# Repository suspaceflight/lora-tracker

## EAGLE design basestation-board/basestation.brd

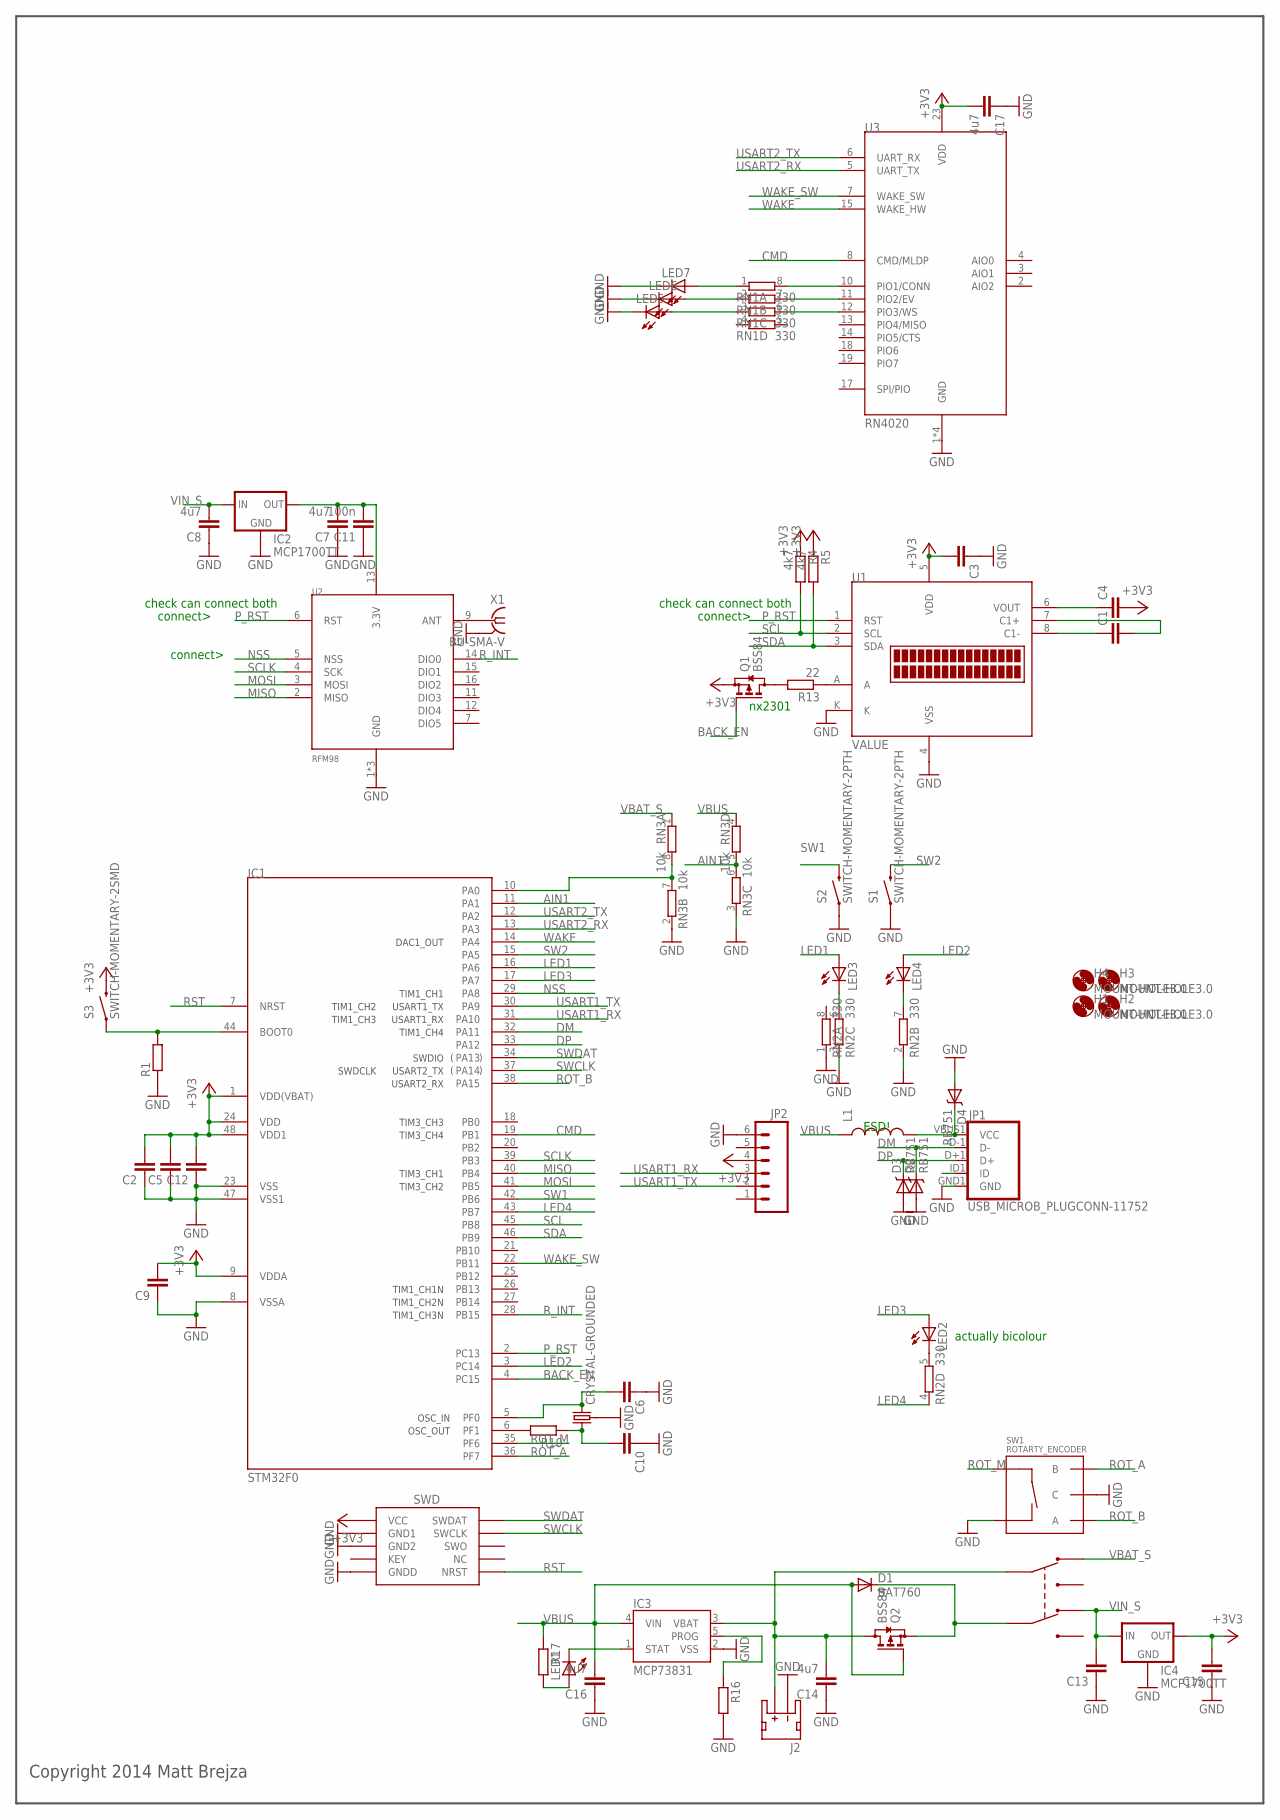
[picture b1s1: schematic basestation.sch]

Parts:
C1, C2, C3, C4, C5, C6, C9, C10, C12, C13, C15: C-EUC0603; C0603
C7, C8, C14, C16, C17: 4u7; C0603
C11: 100n; C0603
D1: BAT760; SOD323-R
D2, D3, D4: RB751; SOD-523
H1, H2, H3, H4: MOUNT-HOLE3.0; 3,0
IC1: STM32F0; TQFP48
IC2, IC4: MCP1700TT; SOT23
IC3: MCP73831; SOT23-5
J1: SWD_SHROUD_SMD; SWD_SMD_SHROUD
J2: JST_2MM_MALE; JST-2-SMD
JP1: USB_MICROB_PLUGCONN-11752; USB-B-MICRO-SMD_V03
JP2: M06SMD; 1X06-SMD
L1: INDUCTOR0603; 0603
LED1, LED5, LED6, LED7: LEDCHIP-LED0805; CHIP-LED0805
LED2: LED5MM
LED3, LED4: LED3MM
Q1, Q2: BSS84; SOT23
R1, R10, R16, R17: R-EU_R0603; R0603
R4, R5: 4k7; R0603
R13: 22; R0603
RN1, RN2: 330; EXB38V
RN3: 10k; EXB38V
S1, S2: SWITCH-MOMENTARY-2PTH; TACTILE-PTH
S3: SWITCH-MOMENTARY-2SMD; TACTILE_SWITCH_SMD
SW1: ROTARTY_ENCODER; ROTARY_ENC_PLAIN
U1: NHD-C0216CIZ-FSW
U2: RFM98; RFM97
U3: RN4020
U$1: DPDTSLIDE
X1: BU-SMA-V
X2: CRYSTAL-GROUNDED; CRYSTAL-SMD-5X3

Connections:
3.3V: C7.2, C11.2, IC2.2 (OUT), U2.13 (3.3V)
+3V3: C2.2, C3.2, C4.2, C5.2, C9.2, C12.2, C15.2, C17.2, IC1.1 (VDD(VBAT)), IC1.9 (VDDA), IC1.24 (VDD), IC1.48 (VDD1), IC4.2 (OUT), J1.1 (VCC), JP2.4, Q1.2 (S), R4.1, R5.1, S3.3 (2), U1.5 (VDD), U3.23 (VDD)
AIN1: IC1.11 (PA1), RN3.5 (2), RN3.6 (2)
BACK_EN: IC1.4 (PC15), Q1.1 (G)
CMD: IC1.19 (PB1), U3.8 (CMD/MLDP)
DM: D2.C, IC1.32 (PA11), JP1.D-1 (D-)
DP: D3.C, IC1.33 (PA12), JP1.D+1 (D+)
GND: C2.1, C3.1, C5.1, C6.1, C7.1, C8.1, C9.1, C10.1, C11.1, C12.1, C13.1, C14.1, C15.1, C16.1, C17.1, D2.A, D3.A, D4.A, IC1.8 (VSSA), IC1.23 (VSS), IC1.47 (VSS1), IC2.1 (GND), IC3.2 (VSS), IC4.1 (GND), J1.3 (GND1), J1.5 (GND2), J1.9 (GNDD), J2.1 (-), JP1.GND1 (GND), JP2.6, LED5.C, LED6.C, LED7.C, R1.1, R16.2, RN2.1, RN2.2 (1), RN2.3 (1), RN3.2 (1), RN3.3 (1), S1.1, S2.1, SW1.C, SW1.SW-, U1.4 (VSS), U1.K, U2.1 (GND), U2.8 (GND), U2.10 (GND), U3.1 (GND), U3.9 (GND), U3.16 (GND), U3.24 (GND), X1.2, X1.3 (2), X1.4 (2), X1.5 (2), X2.2 (3), X2.4 (3)
LED1: IC1.16 (PA6), LED3.A
LED2: IC1.3 (PC14), LED4.A
LED3: IC1.17 (PA7), LED2.A
LED4: IC1.43 (PB7), RN2.4 (1)
MISO: IC1.40 (PB4), U2.2 (MISO)
MOSI: IC1.41 (PB5), U2.3 (MOSI)
unnamed: U2.9 (ANT), X1.1
unnamed: D1.C, Q2.2 (S), U$1.2X (COM1)
unnamed: Q1.3 (D), R13.2
unnamed: IC1.44 (BOOT0), R1.2, S3.1
unnamed: RN1.8 (2), U3.10 (PIO1/CONN)
unnamed: LED3.K (C), RN2.6 (2)
unnamed: IC3.5 (PROG), R16.1
unnamed: C1.1, U1.8 (C1-)
unnamed: C1.2, U1.7 (C1+)
unnamed: LED4.K (C), RN2.7 (2)
unnamed: LED2.K (C), RN2.5 (2)
unnamed: C4.1, U1.6 (VOUT)
unnamed: RN1.7 (2), U3.11 (PIO2/EV)
unnamed: RN1.6 (2), U3.12 (PIO3/WS)
unnamed: LED7.A, RN1.1
unnamed: LED6.A, RN1.2 (1)
unnamed: LED5.A, RN1.3 (1)
unnamed: R13.1, U1.A
unnamed: IC1.10 (PA0), RN3.7 (2), RN3.8 (2)
unnamed: IC3.1 (STAT), LED1.C
unnamed: IC1.6 (PF1), R10.2
unnamed: C6.2, IC1.5 (PF0), X2.1 (2)
unnamed: C10.2, R10.1, X2.3 (1)
unnamed: C14.2, IC3.3 (VBAT), J2.2 (+), Q2.3 (D), U$1.1X (COM0)
unnamed: LED1.A, R17.2
unnamed: D4.C, JP1.VBUS1 (VCC), L1.2
NSS: IC1.29 (PA8), U2.5 (NSS)
P_RST: IC1.2 (PC13), U1.1 (RST), U2.6 (RST)
ROT_A: IC1.36 (PF7), SW1.B
ROT_B: IC1.38 (PA15), SW1.A
ROT_M: IC1.35 (PF6), SW1.SW+
RST: IC1.7 (NRST), J1.10 (NRST)
R_INT: IC1.28 (PB15), U2.14 (DIO0)
SCL: IC1.45 (PB8), R4.2, U1.2 (SCL)
SCLK: IC1.39 (PB3), U2.4 (SCK)
SDA: IC1.46 (PB9), R5.2, U1.3 (SDA)
SW1: IC1.42 (PB6), S2.3 (2)
SW2: IC1.15 (PA5), S1.3 (2)
SWCLK: IC1.37 (PA14), J1.4 (SWCLK)
SWDAT: IC1.34 (PA13), J1.2 (SWDAT)
USART1_RX: IC1.31 (PA10), JP2.3
USART1_TX: IC1.30 (PA9), JP2.2
USART2_RX: IC1.13 (PA3), U3.5 (UART_TX)
USART2_TX: IC1.12 (PA2), U3.6 (UART_RX)
VBAT_S: RN3.1, U$1.1A (NC0)
VBUS: C16.2, D1.A, IC3.4 (VIN), L1.1, Q2.1 (G), R17.1, RN3.4 (1)
VIN_S: C8.2, C13.2, IC2.3 (IN), IC4.3 (IN), U$1.2A (NC1)
WAKE: IC1.14 (PA4), U3.15 (WAKE_HW)
WAKE_SW: IC1.22 (PB11), U3.7 (WAKE_SW)

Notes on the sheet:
actually bicolour
connect>
nx2301
ESD!
check can connect both
Copyright 2014 Matt Brejza

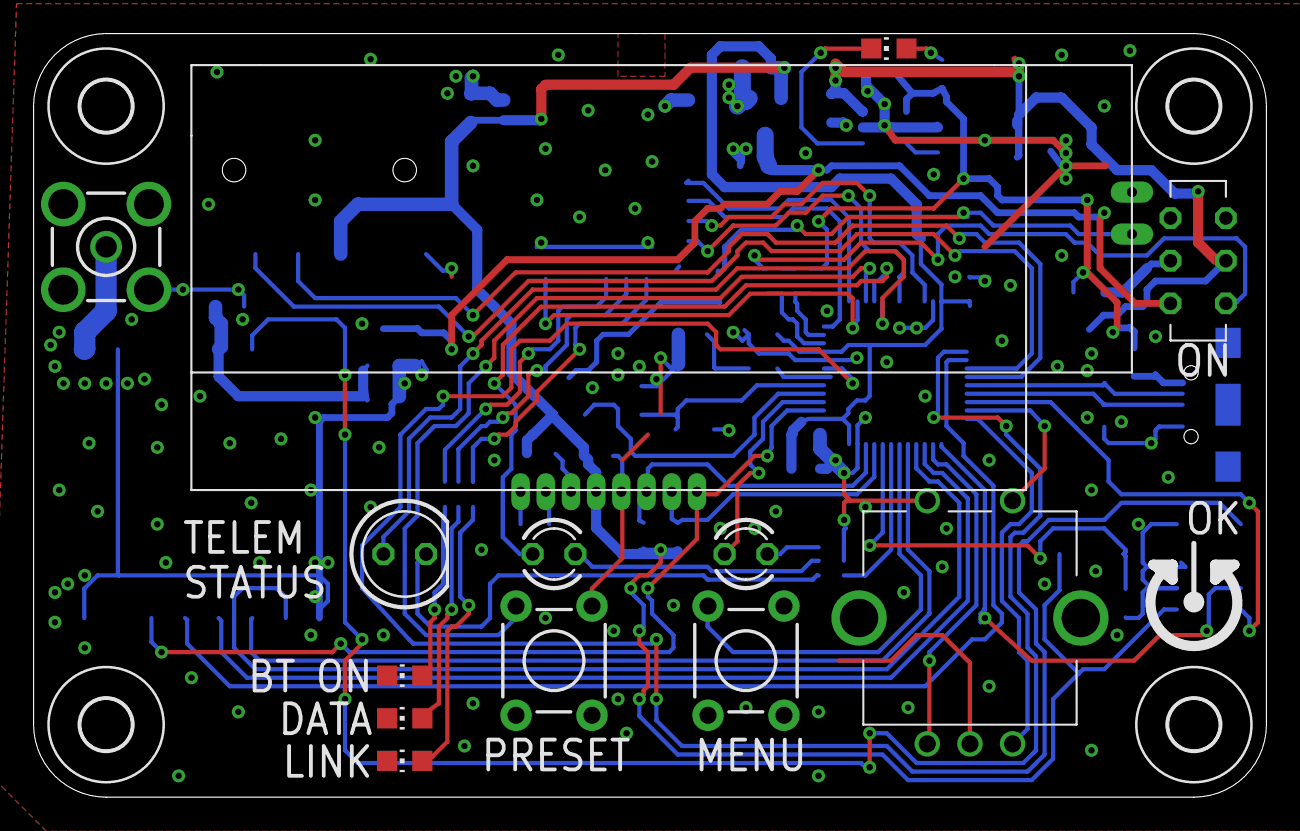
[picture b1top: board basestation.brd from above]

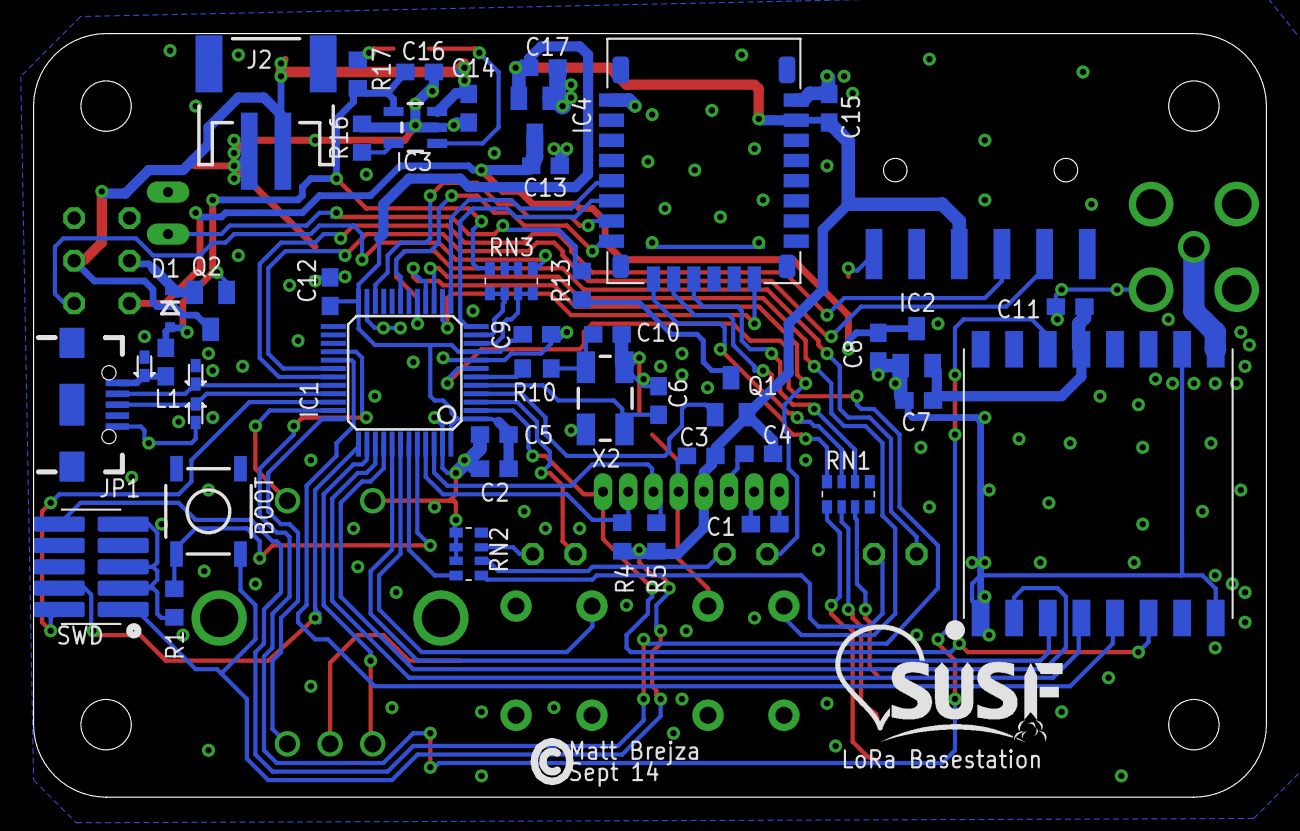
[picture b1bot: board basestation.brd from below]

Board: 2 copper layers, 73.4 x 45.5 mm, 64 parts (47 on the bottom side), 63 nets.

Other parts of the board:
U$2: SUSF-XSM

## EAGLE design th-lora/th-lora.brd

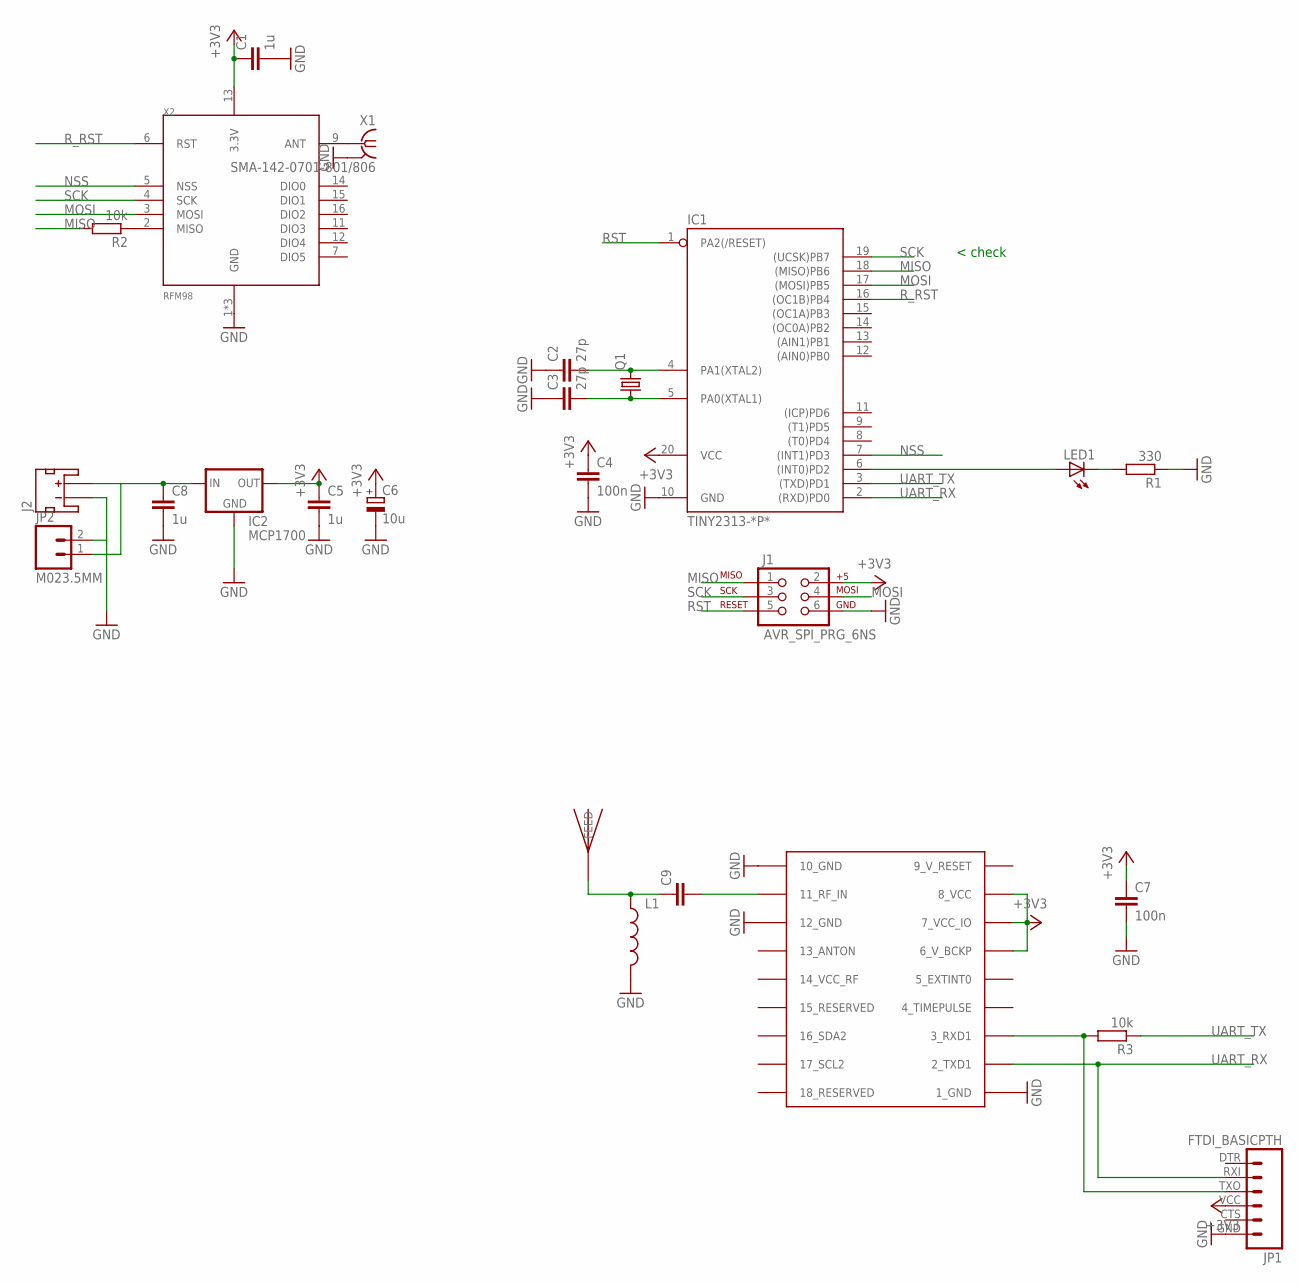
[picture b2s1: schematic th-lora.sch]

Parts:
C1, C5, C8: 1u; C050-025X075
C2, C3: 27p; C050-025X075
C4, C7: 100n; C050-025X075
C6: 10u; E2,5-5
C9: C-EUC0603; C0603
IC1: TINY2313-*P*; DIL20
IC2: MCP1700; TO92-INLINE
J1: AVR_SPI_PRG_6NS; 2X3-NS
J2: JST_2MM_MALE; JST-2-SMD
JP1: FTDI_BASICPTH; FTDI_BASIC
JP2: M023.5MM; SCREWTERMINAL-3.5MM-2
L1: INDUCTOR0603; 0603
LED1: LED3MM
Q1: CRYSTALHC49S; HC49/S
R1: 330; 0204/7
R2, R3: 10k; 0204/7
U$3: JTI_ANTENNA-1575AT43A40
X1: SMA-142-0701-801/806; J502-ND-142-0701-801/806
X2: RFM98; RFM97
X3: UBLOX_MAX

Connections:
9_V_RESET: X3.9_V_RESET
+3V3: C1.1, C4.1, C5.1, C6.+, C7.1, IC1.20 (VCC), IC2.VOUT (OUT), J1.2, JP1.VCC (4), X2.13 (3.3V), X3.6_V_BCKP, X3.7_VCC_IO, X3.8_VCC
GND: C1.2, C2.1, C3.1, C4.2, C5.2, C6.-, C7.2, C8.2, IC1.10 (GND), IC2.GND, J1.6, J2.1 (-), JP1.GND (6), JP2.2, L1.2, R1.1, X1.G@1 (2), X1.G@2 (2), X1.G@3 (2), X1.G@4 (2), X2.1 (GND), X2.8 (GND), X2.10 (GND), X3.1_GND, X3.10_GND, X3.12_GND
MISO: IC1.18 ((MISO)PB6), J1.1, R2.2
MOSI: IC1.17 ((MOSI)PB5), J1.4, X2.3 (MOSI)
unnamed: C9.2, X3.11_RF_IN
unnamed: X1.1, X2.9 (ANT)
unnamed: LED1.K (C), R1.2
unnamed: C9.1, L1.1, U$3.FEED
unnamed: C2.2, IC1.4 (PA1(XTAL2)), Q1.2
unnamed: C3.2, IC1.5 (PA0(XTAL1)), Q1.1
unnamed: C8.1, IC2.VIN (IN), J2.2 (+), JP2.1
unnamed: IC1.6 ((INT0)PD2), LED1.A
unnamed: JP1.TXO (3), R3.2, X3.3_RXD1
unnamed: R2.1, X2.2 (MISO)
NSS: IC1.7 ((INT1)PD3), X2.5 (NSS)
RST: IC1.1 (PA2(/RESET)), J1.5
R_RST: IC1.16 ((OC1B)PB4), X2.6 (RST)
SCK: IC1.19 ((UCSK)PB7), J1.3, X2.4 (SCK)
UART_RX: IC1.2 ((RXD)PD0), JP1.RXI (2), X3.2_TXD1
UART_TX: IC1.3 ((TXD)PD1), R3.1

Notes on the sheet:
< check

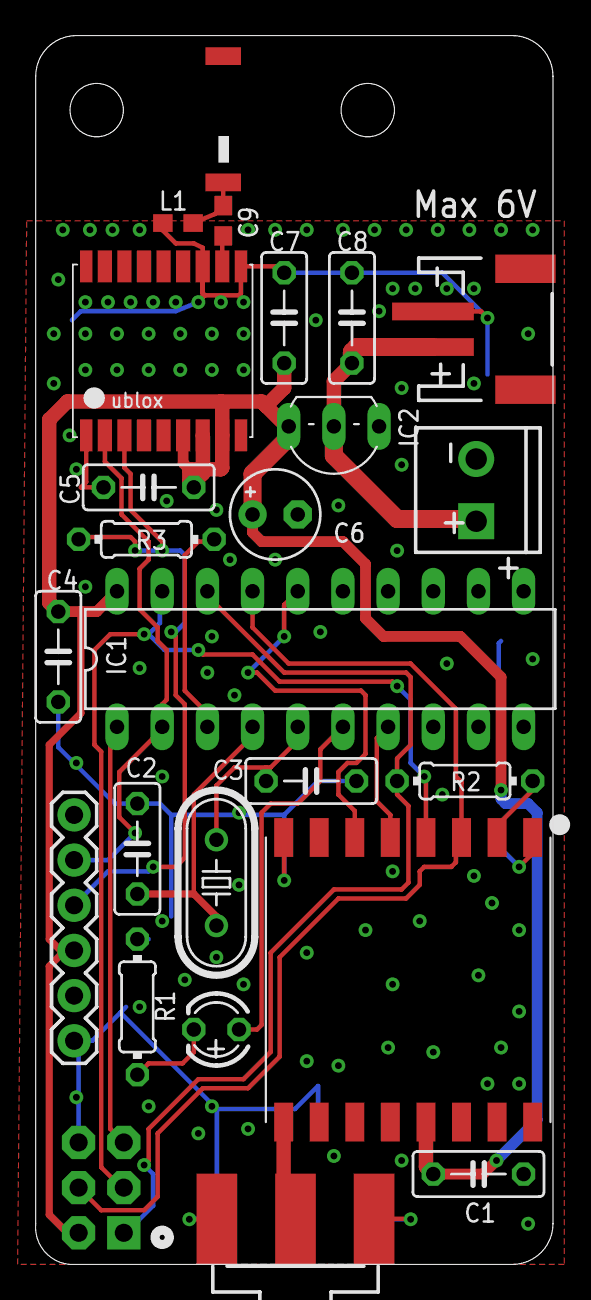
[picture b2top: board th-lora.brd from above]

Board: 2 copper layers, 29.1 x 69.1 mm, 26 parts (1 on the bottom side), 20 nets.

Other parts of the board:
U$4: SUSF-XSM

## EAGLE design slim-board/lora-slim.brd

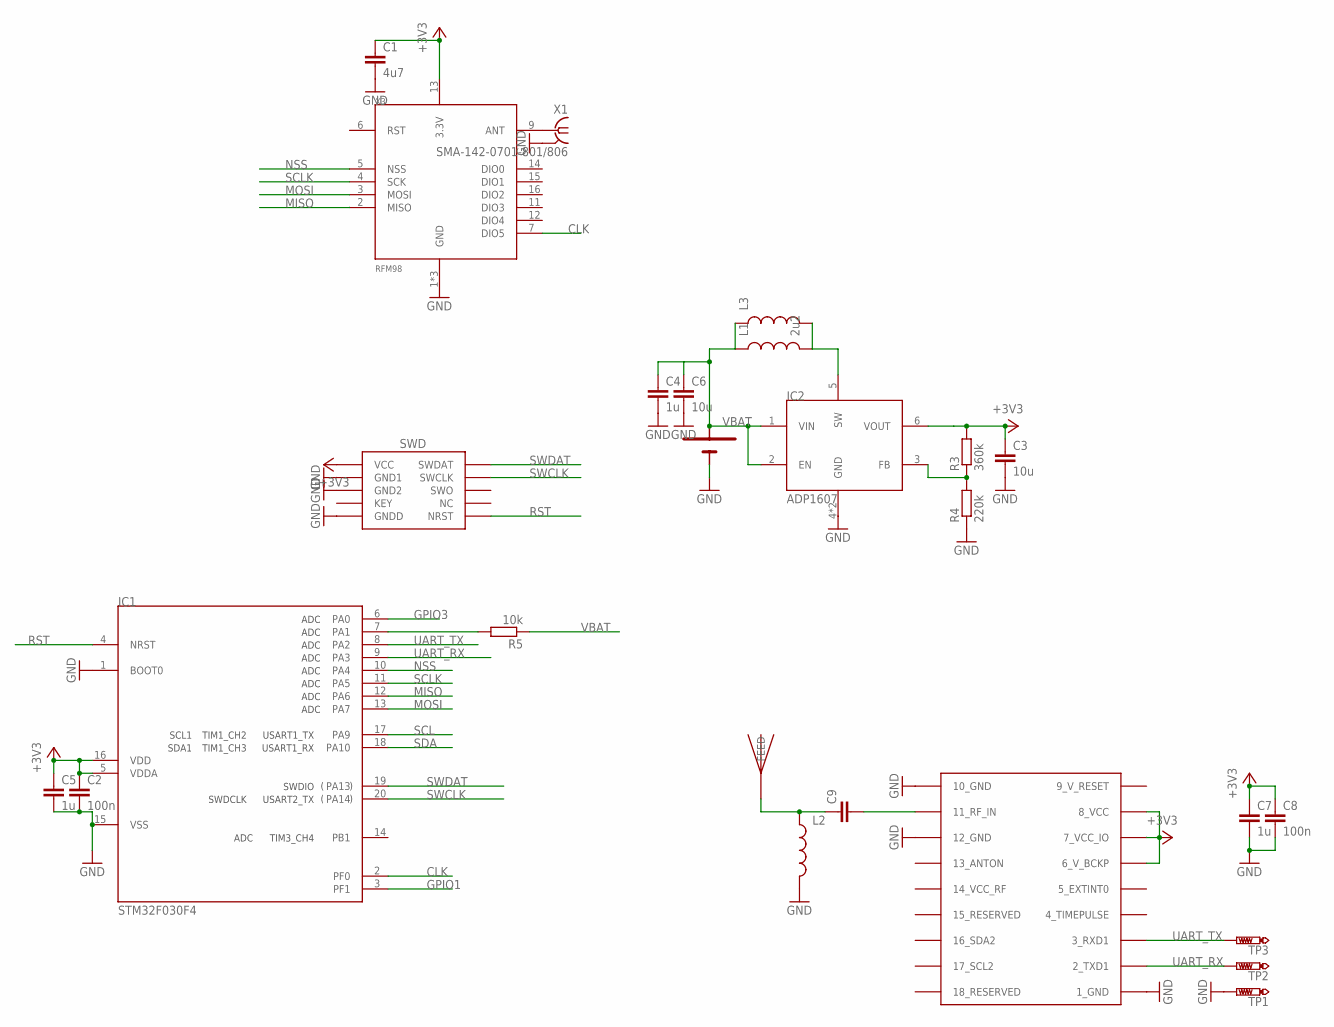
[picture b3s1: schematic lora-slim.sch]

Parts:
C1: 4u7; C0603
C2, C8: 100n; C0603
C3, C6: 10u; C0805
C4, C5, C7: 1u; C0603
C9: C-EUC0603; C0603
IC1: STM32F030F4; TSSOP20
IC2: ADP1607; LFCSP6
J1: SWD_PTH_SHROUD
L1: 2u2; 0805
L2: INDUCTOR0603; 0603
L3: INDUCTOR1210; 1210
R3: 360k; R0603
R4: 220k; R0603
R5: 10k; R0603
TP1, TP2, TP3: PTR1B1,27; B1,27
U$5: JTI_ANTENNA-1575AT43A40
U$6: KEYSTONE-53; KEYSTONE53
X1: SMA-142-0701-801/806; J502-ND-142-0701-801/806
X2: UBLOX_MAX
X3: RFM98; RFM97

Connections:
9_V_RESET: X2.9_V_RESET
+3V3: C1.1, C2.1, C3.1, C5.1, C7.1, C8.1, IC1.5 (VDDA), IC1.16 (VDD), IC2.6 (VOUT), J1.1 (VCC), R3.2, X2.6_V_BCKP, X2.7_VCC_IO, X2.8_VCC, X3.13 (3.3V)
CLK: IC1.2 (PF0), X3.7 (DIO5)
GND: C1.2, C2.2, C3.2, C4.2, C5.2, C6.2, C7.2, C8.2, IC1.1 (BOOT0), IC1.15 (VSS), IC2.4 (GND), IC2.EP (GND), J1.3 (GND1), J1.5 (GND2), J1.9 (GNDD), L2.2, R4.1, TP1.TP, U$6.N1 (-), U$6.N2 (-), X1.G@1 (2), X1.G@2 (2), X1.G@3 (2), X1.G@4 (2), X2.1_GND, X2.10_GND, X2.12_GND, X3.1 (GND), X3.8 (GND), X3.10 (GND)
GPIO1: IC1.3 (PF1)
GPIO3: IC1.6 (PA0)
MISO: IC1.12 (PA6), X3.2 (MISO)
MOSI: IC1.13 (PA7), X3.3 (MOSI)
unnamed: C9.2, X2.11_RF_IN
unnamed: X1.1, X3.9 (ANT)
unnamed: IC2.5 (SW), L1.2, L3.2
unnamed: C9.1, L2.1, U$5.FEED
unnamed: IC2.3 (FB), R3.1, R4.2
unnamed: IC1.7 (PA1), R5.2
NSS: IC1.10 (PA4), X3.5 (NSS)
RST: IC1.4 (NRST), J1.10 (NRST)
SCL: IC1.17 (PA9)
SCLK: IC1.11 (PA5), X3.4 (SCK)
SDA: IC1.18 (PA10)
SWCLK: IC1.20 (PA14), J1.4 (SWCLK)
SWDAT: IC1.19 (PA13), J1.2 (SWDAT)
UART_RX: IC1.9 (PA3), TP2.TP, X2.2_TXD1
UART_TX: IC1.8 (PA2), TP3.TP, X2.3_RXD1
VBAT: C4.1, C6.1, IC2.1 (VIN), IC2.2 (EN), L1.1, L3.1, R5.1, U$6.P1 (+), U$6.P2 (+)

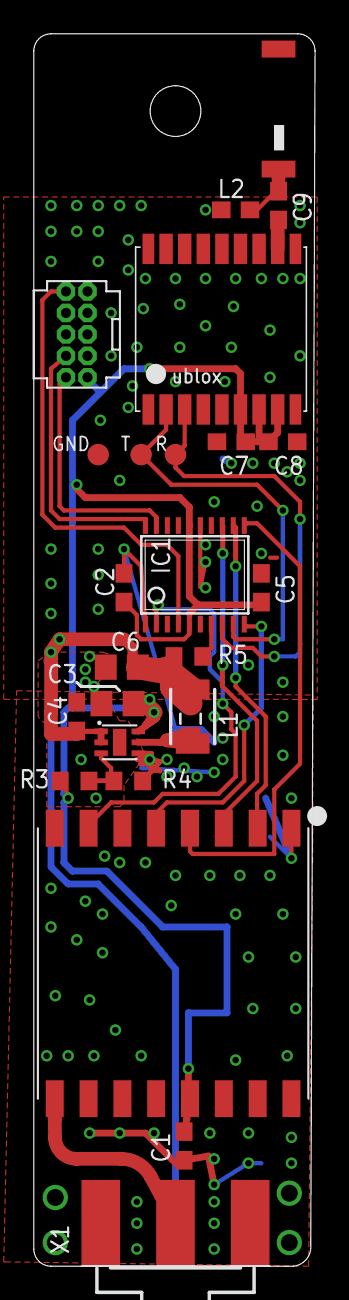
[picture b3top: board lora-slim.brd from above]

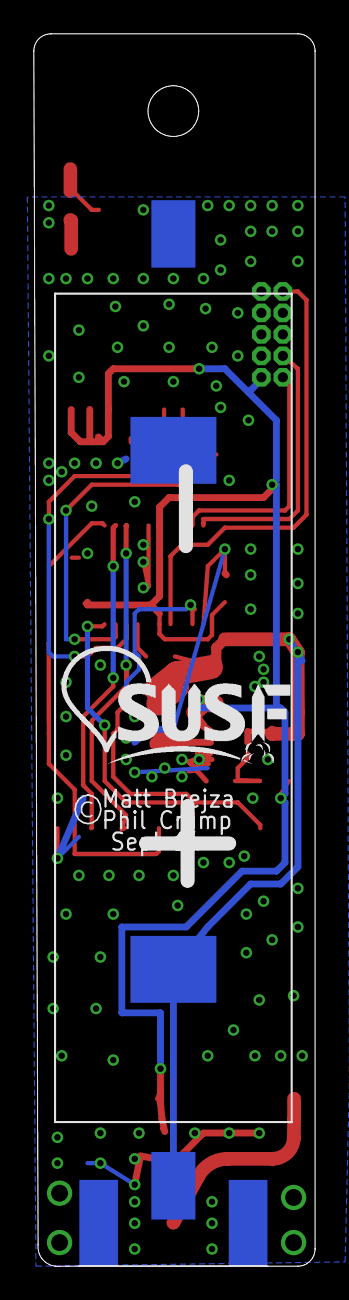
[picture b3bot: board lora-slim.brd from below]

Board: 2 copper layers, 16.6 x 72.9 mm, 27 parts (2 on the bottom side), 19 nets.

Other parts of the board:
U$1: SUSF-XSM

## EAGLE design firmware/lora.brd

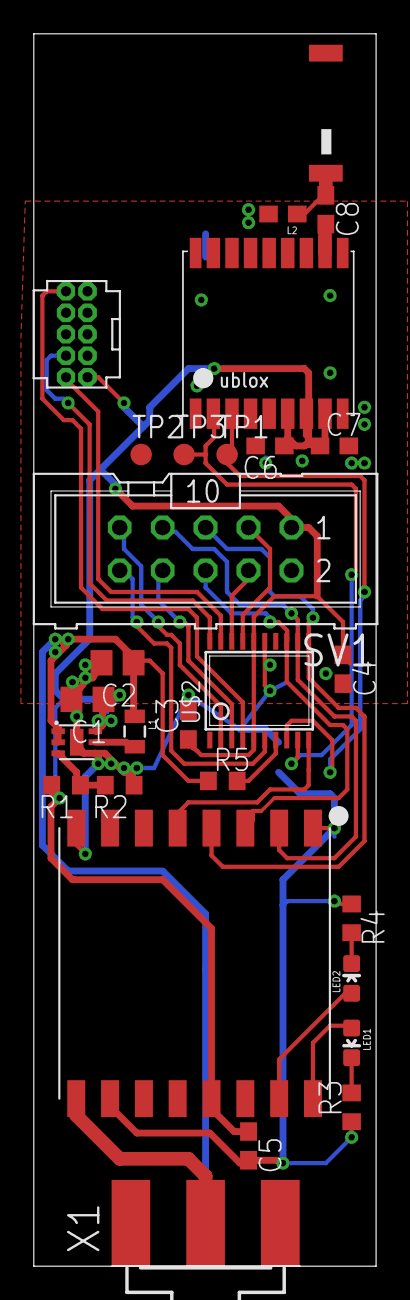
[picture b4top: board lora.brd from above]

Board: 2 copper layers, 20.2 x 72.9 mm, 29 parts (1 on the bottom side), 27 nets.

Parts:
C1, C2: C0805
C3, C4, C5, C6, C7, C8: C0603
J1: SWD_PTH_SHROUD
L1: 0805
L2: 0603
LED1, LED2: LED-0603
R1, R2, R3, R4, R5: R0603
SV1: ML10
TP1, TP2, TP3: PTR1B1,27; B1,27
U$1: KEYSTONE-53; KEYSTONE53
U$2: STM32F030F4; TSSOP20
U$3: UBLOX_MAX
U$4: JTI_ANTENNA-1575AT43A40
U$6: RFM98; RFM97
U$7: ADP1607; LFCSP6
X1: SMA-142-0701-801/806; J502-ND-142-0701-801/806

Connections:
+3V3: C1.1, C3.1, C4.1, C5.1, C6.1, C7.1, J1.1, R1.2, SV1.1, U$2.5, U$2.16, U$3.6_V_BCKP, U$3.7_VCC_IO, U$3.8_VCC, U$6.13, U$7.6
GND: C1.2, C2.2, C3.2, C4.2, C5.2, C6.2, C7.2, J1.3, J1.5, J1.9, L2.2, R2.1, R3.1, R4.1, SV1.2, TP2.TP, U$1.N1, U$1.N2, U$2.15, U$3.1_GND, U$3.10_GND, U$3.12_GND, U$6.1, U$6.8, U$6.10, U$7.4, U$7.EP
GPIO1: SV1.8, U$2.3
GPIO2: SV1.9, U$2.2
GPIO3: SV1.10, U$2.6
MISO: SV1.7, U$2.12, U$6.2
MOSI: SV1.6, U$2.13, U$6.3
unnamed: C8.2, U$3.11_RF_IN
unnamed: U$6.9, X1.1
unnamed: L1.2, U$7.5
unnamed: C8.1, L2.1, U$4.FEED
unnamed: LED1.C, R3.2
unnamed: R1.1, R2.2, U$7.3
unnamed: LED2.C, R4.2
unnamed: LED2.A, U$6.15
unnamed: R5.2, U$2.7
unnamed: LED1.A, U$6.16
NSS: U$2.10, U$6.5
RST: J1.10, U$2.4
SCL: SV1.3, U$2.17
SCLK: SV1.5, U$2.11, U$6.4
SDA: SV1.4, U$2.18
SWCLK: J1.4, U$2.20
SWDAT: J1.2, U$2.19
UART_RX: TP3.TP, U$2.9, U$3.2_TXD1
UART_TX: TP1.TP, U$2.8, U$3.3_RXD1
VBAT: C2.1, L1.1, R5.1, U$1.P1, U$1.P2, U$7.1, U$7.2

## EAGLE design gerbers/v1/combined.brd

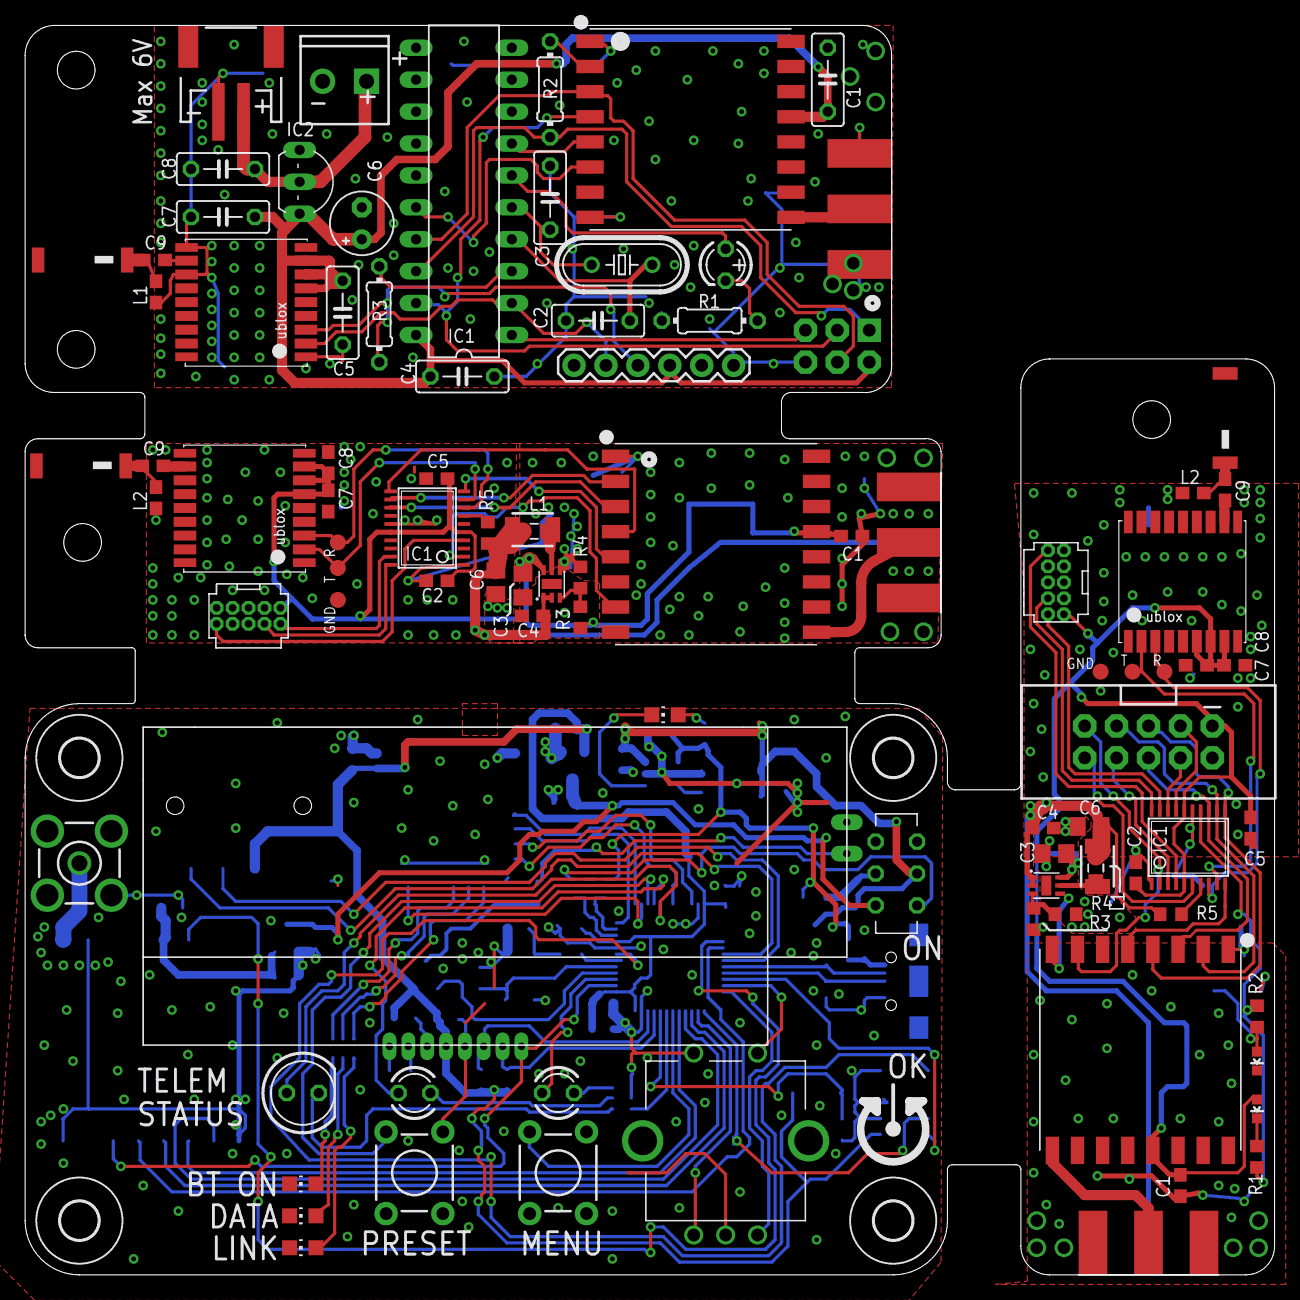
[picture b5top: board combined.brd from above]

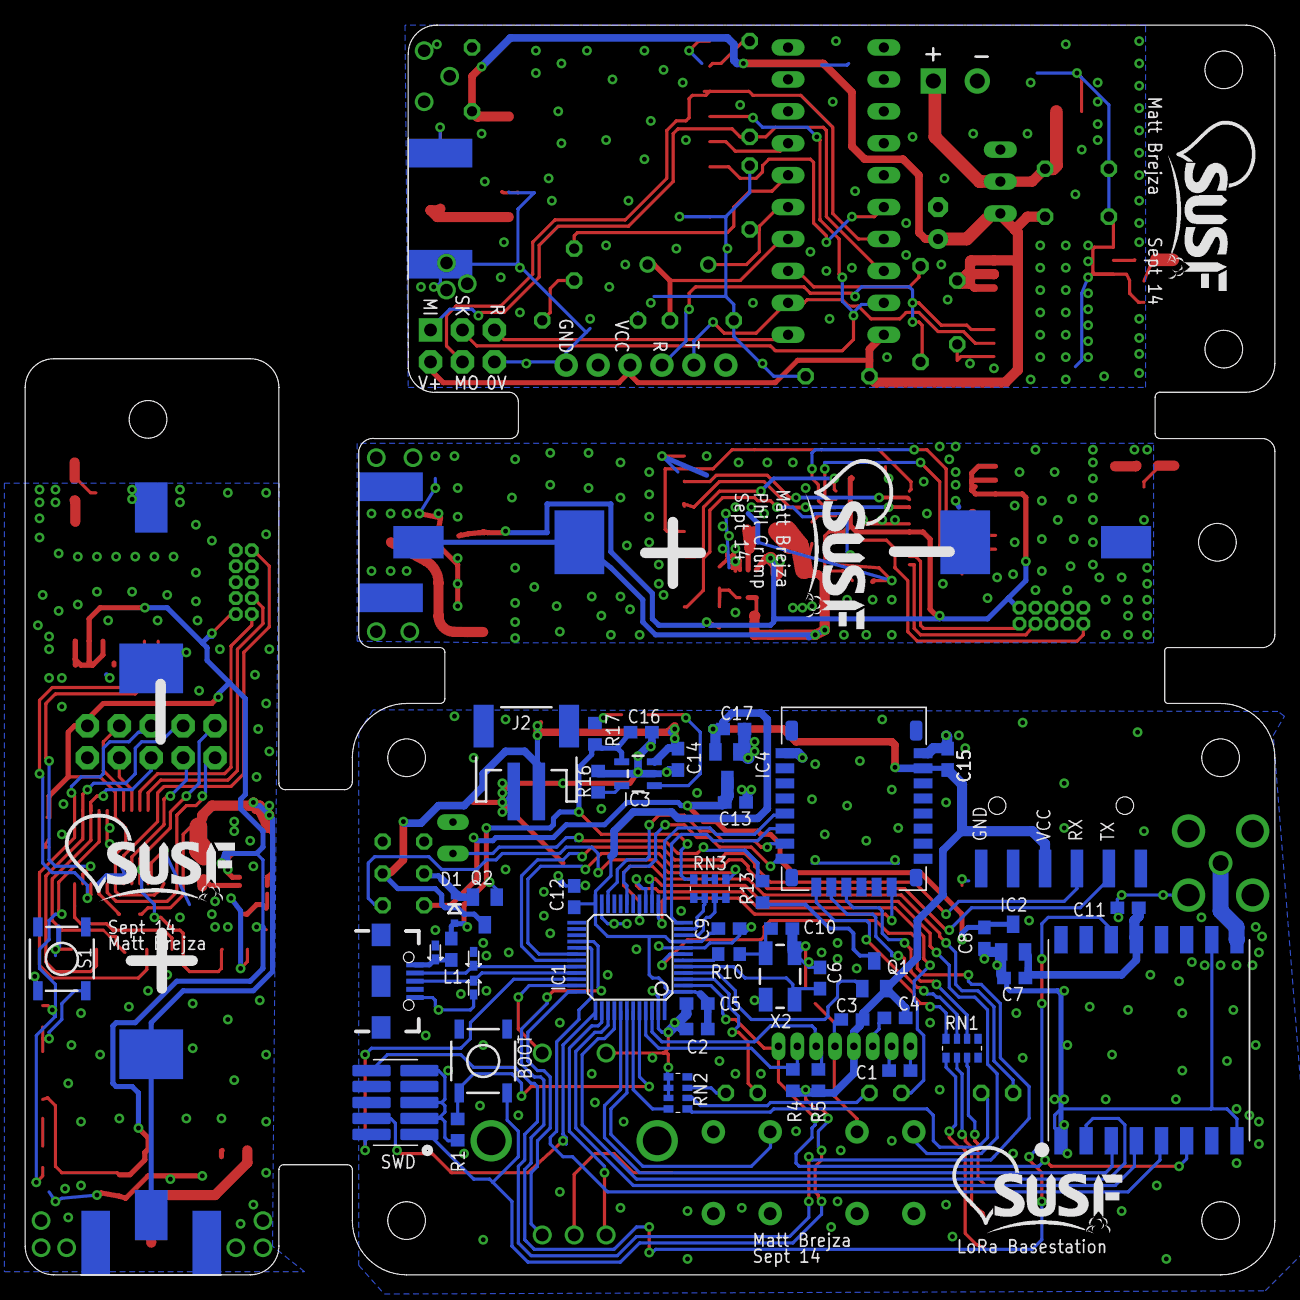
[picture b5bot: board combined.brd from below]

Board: 2 copper layers, 99.4 x 99.4 mm, 150 parts (53 on the bottom side), 127 nets.

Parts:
C1, C2, C3, C4, C5, C6, C9, C10, C12, C13, C15, C25, C34, C36: C0603
C7, C8, C14, C16, C17, C22, C31: 4u7; C0603
C11, C20, C24, C29, C33: 100n; C0603
C18, C19, C27, C28: 10u; C0805
C21, C23, C26, C30, C32, C35: 1u; C0603
C37, C42: 100n; C050-025X075
C38, C39, C43: 1u; C050-025X075
C40, C41: 27p; C050-025X075
C44: 10u; E2,5-5
D1: BAT760; SOD323-R
D2, D3, D4: RB751; SOD-523
H1, H2, H3, H4: MOUNT-HOLE3.0; 3,0
IC1: STM32F0; TQFP48
IC2, IC4: MCP1700TT; SOT23
IC3: MCP73831; SOT23-5
IC5, IC7: STM32F030F4; TSSOP20
IC6, IC8: ADP1607; LFCSP6
IC9: TINY2313-*P*; DIL20
IC10: MCP1700; TO92-INLINE
J1: SWD_SHROUD_SMD; SWD_SMD_SHROUD
J2, J6: JST-2-SMD
J3, J4: SWD_PTH_SHROUD
J5: AVR_SPI_PRG_6NS; 2X3-NS
JP1: USB_MICROB_PLUGCONN-11752; USB-B-MICRO-SMD_V03
JP2: 1X06-SMD
JP3: M05X2SHD; 2X5-SHROUDED
JP4: M023.5MM; SCREWTERMINAL-3.5MM-2
JP5: FTDI_BASICPTH; FTDI_BASIC
L1, L3, L6, L8: 0603
L2, L5: 2u2; 0805
L4, L7: 1210
LED1, LED5, LED6, LED7: CHIP-LED0805
LED2: LED5MM
LED3, LED4, LED10: LED3MM
LED8, LED9: LED-0603
Q1, Q2: BSS84; SOT23
Q3: HC49/S
R1, R10, R16, R17: R0603
R2, R11: 220k; R0603
R3, R9: 360k; R0603
R4, R5: 4k7; R0603
R6, R7: 330; R0603
R8, R12: 10k; R0603
R13: 22; R0603
R14: 330; 0204/7
R15, R18: 10k; 0204/7
RN1, RN2: 330; EXB38V
RN3: 10k; EXB38V
S1, S2: SWITCH-MOMENTARY-2PTH; TACTILE-PTH
S3, S4: SWITCH-MOMENTARY-2SMD; TACTILE_SWITCH_SMD
SW1: ROTARTY_ENCODER; ROTARY_ENC_PLAIN
TP1, TP2, TP3, TP4, TP5, TP6: PTR1B1,27; B1,27
U1: NHD-C0216CIZ-FSW
U2: RFM98; RFM97
U3: RN4020
U$1: DPDTSLIDE
U$2, U$3, U$8, U$10: SUSF-XSM
U$4, U$5, U$9: JTI_ANTENNA-1575AT43A40
U$6, U$7: KEYSTONE-53; KEYSTONE53
X1: BU-SMA-V
X2: CRYSTAL-GROUNDED; CRYSTAL-SMD-5X3
X3, X6, X9: UBLOX_MAX
X4, X7, X10: SMA-142-0701-801/806; J502-ND-142-0701-801/806
X5, X8, X11: RFM98; RFM97

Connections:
3.3V: C7.2, C11.2, IC2.2, U2.13
+3V1: C18.1, C20.1, C21.1, C22.1, C23.1, C24.1, IC5.5, IC5.16, IC6.6, J3.1, JP3.1, LED9.A, R3.2, X3.6_V_BCKP, X3.7_VCC_IO, X3.8_VCC, X5.13
+3V2: C27.1, C29.1, C30.1, C31.1, C32.1, C33.1, IC7.5, IC7.16, IC8.6, J4.1, R9.2, X6.6_V_BCKP, X6.7_VCC_IO, X6.8_VCC, X8.13
+3V3: C2.2, C3.2, C4.2, C5.2, C9.2, C12.2, C15.2, C17.2, IC1.1, IC1.9, IC1.24, IC1.48, IC4.2, J1.1, JP2.4, Q1.2, R4.1, R5.1, S3.3, U1.5, U3.23
+3V4: C37.1, C38.1, C42.1, C43.1, C44.+, IC9.20, IC10.VOUT, J5.2, JP5.VCC, X9.6_V_BCKP, X9.7_VCC_IO, X9.8_VCC, X11.13
AIN1: IC1.11, RN3.5, RN3.6
BACK_EN: IC1.4, Q1.1
CLK: IC7.2, X8.7
CMD: IC1.19, U3.8
DM: D2.C, IC1.32, JP1.D-1
DP: D3.C, IC1.33, JP1.D+1
GND: C2.1, C3.1, C5.1, C6.1, C7.1, C8.1, C9.1, C10.1, C11.1, C12.1, C13.1, C14.1, C15.1, C16.1, C17.1, D2.A, D3.A, D4.A, IC1.8, IC1.23, IC1.47, IC2.1, IC3.2, IC4.1, J1.3, J1.5, J1.9, J2.1, JP1.GND1, JP2.6, LED5.C, LED6.C, LED7.C, R1.1, R16.2, RN2.1, RN2.2, RN2.3, RN3.2, RN3.3, S1.1, S2.1, SW1.C, SW1.SW-, U1.4, U1.K, U2.1, U2.8, U2.10, U3.1, U3.9, U3.16, U3.24, X1.2, X1.3, X1.4, X1.5, X2.2, X2.4
GND2: C27.2, C28.2, C29.2, C30.2, C31.2, C32.2, C33.2, C35.2, IC7.1, IC7.15, IC8.4, IC8.EP, J4.3, J4.5, J4.9, L6.2, R11.1, TP6.TP, U$7.N1, U$7.N2, X6.1_GND, X6.10_GND, X6.12_GND, X7.G@1, X7.G@2, X7.G@3, X7.G@4, X8.1, X8.8, X8.10
GND3: C18.2, C19.2, C20.2, C21.2, C22.2, C23.2, C24.2, C26.2, C37.2, C38.2, C39.2, C40.1, C41.1, C42.2, C43.2, C44.-, IC5.1, IC5.15, IC6.4, IC6.EP, IC9.10, IC10.GND, J3.3, J3.5, J3.9, J5.6, J6.1, JP3.2, JP4.2, JP5.GND, L3.2, L8.2, LED8.C, R2.1, R14.1, S4.1, TP1.TP, U$6.N1, U$6.N2, X3.1_GND, X3.10_GND, X3.12_GND, X4.G@1, X4.G@2, X4.G@3, X4.G@4, X5.1, X5.8, X5.10, X9.1_GND, X9.10_GND, X9.12_GND, X10.G@1, X10.G@2, X10.G@3, X10.G@4, X11.1, X11.8, X11.10
GPIO1: IC5.3, JP3.8
GPIO2: IC5.2, JP3.9, X5.7
GPIO3: IC5.6, JP3.10
LED1: IC1.16, LED3.A
LED2: IC1.3, LED4.A
LED3: IC1.17, LED2.A
LED4: IC1.43, RN2.4
MISO: IC1.40, U2.2
MISO1: IC5.12, JP3.7, X5.2
MISO2: IC7.12, X8.2
MISO3: IC9.18, J5.1, R18.2
MOSI: IC1.41, U2.3
MOSI1: IC5.13, JP3.6, X5.3
MOSI2: IC7.13, X8.3
MOSI3: IC9.17, J5.4, X11.3
unnamed: U2.9, X1.1
unnamed: D1.C, Q2.2, U$1.2X
unnamed: Q1.3, R13.2
unnamed: IC1.44, R1.2, S3.1
unnamed: RN1.8, U3.10
unnamed: LED3.K, RN2.6
unnamed: IC3.5, R16.1
unnamed: C1.1, U1.8
unnamed: C1.2, U1.7
unnamed: LED4.K, RN2.7
unnamed: LED2.K, RN2.5
unnamed: C4.1, U1.6
unnamed: RN1.7, U3.11
unnamed: RN1.6, U3.12
unnamed: LED7.A, RN1.1
unnamed: LED6.A, RN1.2
unnamed: LED5.A, RN1.3
unnamed: X4.1, X5.9
unnamed: IC6.5, L2.2, L4.2
unnamed: IC6.3, R2.2, R3.1
unnamed: LED9.C, R7.2
unnamed: R13.1, U1.A
unnamed: IC5.7, R8.2
unnamed: C25.2, X3.11_RF_IN
unnamed: C25.1, L3.1, U$5.FEED
unnamed: IC1.10, RN3.7, RN3.8
unnamed: IC3.1, LED1.C
unnamed: IC1.6, R10.2
unnamed: C6.2, IC1.5, X2.1
unnamed: C10.2, R10.1, X2.3
unnamed: C14.2, IC3.3, J2.2, Q2.3, U$1.1X
unnamed: LED1.A, R17.2
unnamed: D4.C, JP1.VBUS1, L1.2
unnamed: IC5.14, R6.2, R7.1
unnamed: LED8.A, R6.1, S4.3
unnamed: X7.1, X8.9
unnamed: IC8.5, L5.2, L7.2
unnamed: IC8.3, R9.1, R11.2
unnamed: IC7.7, R12.2
unnamed: C34.2, X6.11_RF_IN
unnamed: C34.1, L6.1, U$4.FEED
unnamed: X10.1, X11.9
unnamed: C36.2, X9.11_RF_IN
unnamed: C36.1, L8.1, U$9.FEED
unnamed: C39.1, IC10.VIN, J6.2, JP4.1
unnamed: C40.2, IC9.4, Q3.2
unnamed: C41.2, IC9.5, Q3.1
unnamed: LED10.K, R14.2
unnamed: IC9.6, LED10.A
unnamed: JP5.TXO, R15.2, X9.3_RXD1
unnamed: R18.1, X11.2
NSS: IC1.29, U2.5
NSS1: IC5.10, X5.5
NSS2: IC7.10, X8.5
NSS3: IC9.7, X11.5
P_RST: IC1.2, U1.1, U2.6
ROT_A: IC1.36, SW1.B
ROT_B: IC1.38, SW1.A
ROT_M: IC1.35, SW1.SW+
RST: IC1.7, J1.10
RST1: IC5.4, J3.10
RST2: IC7.4, J4.10
RST3: IC9.1, J5.5
R_INT: IC1.28, U2.14
R_RST: IC9.16, X11.6
SCK: IC9.19, J5.3, X11.4
SCL: IC1.45, R4.2, U1.2
SCL1: IC5.17, JP3.3
SCLK: IC1.39, U2.4
SCLK1: IC5.11, JP3.5, X5.4
SCLK2: IC7.11, X8.4
SDA: IC1.46, R5.2, U1.3
SDA1: IC5.18, JP3.4
SW1: IC1.42, S2.3
SW2: IC1.15, S1.3
SWCLK: IC1.37, J1.4
SWCLK1: IC5.20, J3.4
SWCLK2: IC7.20, J4.4
SWDAT: IC1.34, J1.2
SWDAT1: IC5.19, J3.2
SWDAT2: IC7.19, J4.2
UART_RX: IC5.9, TP2.TP, X3.2_TXD1
UART_RX1: IC7.9, TP4.TP, X6.2_TXD1
UART_RX2: IC9.2, JP5.RXI, X9.2_TXD1
UART_TX: IC5.8, TP3.TP, X3.3_RXD1
UART_TX1: IC7.8, TP5.TP, X6.3_RXD1
UART_TX2: IC9.3, R15.1
USART1_RX: IC1.31, JP2.3
USART1_TX: IC1.30, JP2.2
USART2_RX: IC1.13, U3.5
USART2_TX: IC1.12, U3.6
VBAT: C19.1, C26.1, IC6.1, IC6.2, L2.1, L4.1, R8.1, U$6.P1, U$6.P2
VBAT1: C28.1, C35.1, IC8.1, IC8.2, L5.1, L7.1, R12.1, U$7.P1, U$7.P2
VBAT_S: RN3.1, U$1.1A
VBUS: C16.2, D1.A, IC3.4, L1.1, Q2.1, R17.1, RN3.4
VIN_S: C8.2, C13.2, IC2.3, IC4.3, U$1.2A
WAKE: IC1.14, U3.15
WAKE_SW: IC1.22, U3.7

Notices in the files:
parts and their libraries:
SparkFun-Electromechanical: Licensing: Creative Commons ShareAlike 4.0 International - https://creativecommons.org/licenses/by-sa/4.0
SparkFun-DiscreteSemi: Licensing: CC v3.0 Share-Alike You are welcome to use this library for commercial purposes.
